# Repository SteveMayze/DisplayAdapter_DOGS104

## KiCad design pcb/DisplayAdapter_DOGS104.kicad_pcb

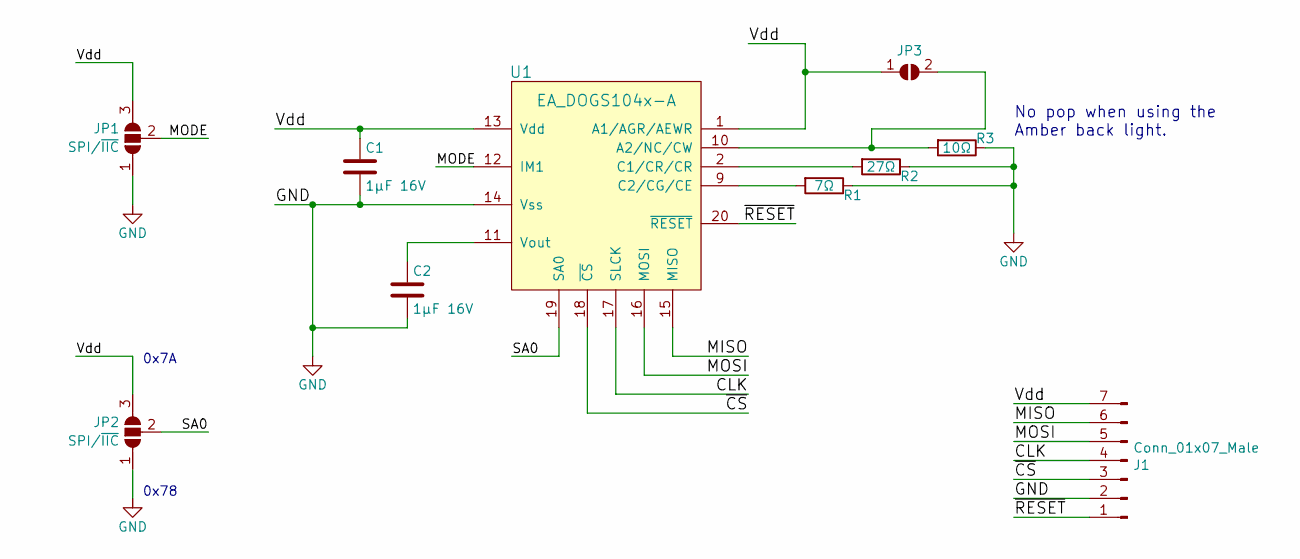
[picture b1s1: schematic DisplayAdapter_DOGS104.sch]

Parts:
C1, C2: 1μF 16V; C_0805_2012Metric_Pad1.15x1.40mm_HandSolder
J1: Conn_01x07_Male; PinHeader_1x07_P2.54mm_Horizontal
JP1, JP2: SPI/~IIC; SolderJumper-3_P1.3mm_Open_RoundedPad1.0x1.5mm_NumberLabels
JP3: SolderJumper_2_Open; SolderJumper-2_P1.3mm_Open_RoundedPad1.0x1.5mm
R1: 7Ω; R_0805_2012Metric_Pad1.15x1.40mm_HandSolder
R2: 27Ω; R_0805_2012Metric_Pad1.15x1.40mm_HandSolder
R3: 10Ω; R_0805_2012Metric_Pad1.15x1.40mm_HandSolder
U1: EA_DOGS104x-A

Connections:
/CLK: J1.4, U1.17 (SLCK~)
/MISO: J1.6, U1.15 (MISO)
/MODE: JP1.2 (C), U1.12 (IM1)
/MOSI: J1.5, U1.16 (MOSI)
/SA0: JP2.2 (C), U1.19 (SA0~)
/Vdd: C1.1, J1.7, JP1.3 (B), JP2.3 (B), JP3.1 (A), U1.1 (A1/AGR/AEWR), U1.13 (Vdd)
/~CS: J1.3, U1.18 (~CS)
/~RESET: J1.1, U1.20 (~RESET)
GND: C1.2, C2.2, J1.2, JP1.1 (A), JP2.1 (A), R1.1, R2.1, R3.1, U1.14 (Vss)
unnamed: C2.1, U1.11 (Vout)
unnamed: JP3.2 (B), R3.2, U1.10 (A2/NC/CW)
unnamed: R1.2, U1.9 (C2/CG/CE)
unnamed: R2.2, U1.2 (C1/CR/CR)

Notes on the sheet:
No pop when using the Amber back light.
0x7A
0x78

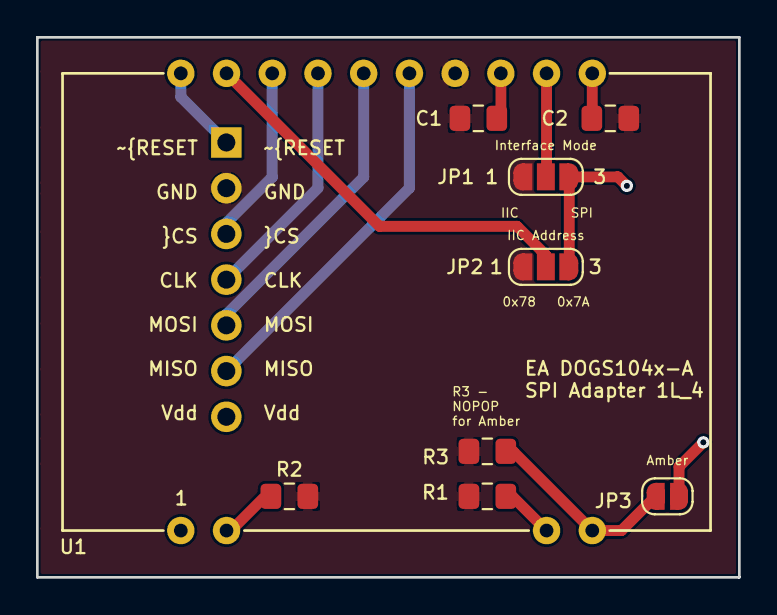
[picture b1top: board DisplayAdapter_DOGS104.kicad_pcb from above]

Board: 2 copper layers, 39.0 x 30.0 mm, 10 parts (1 on the bottom side), 13 nets.

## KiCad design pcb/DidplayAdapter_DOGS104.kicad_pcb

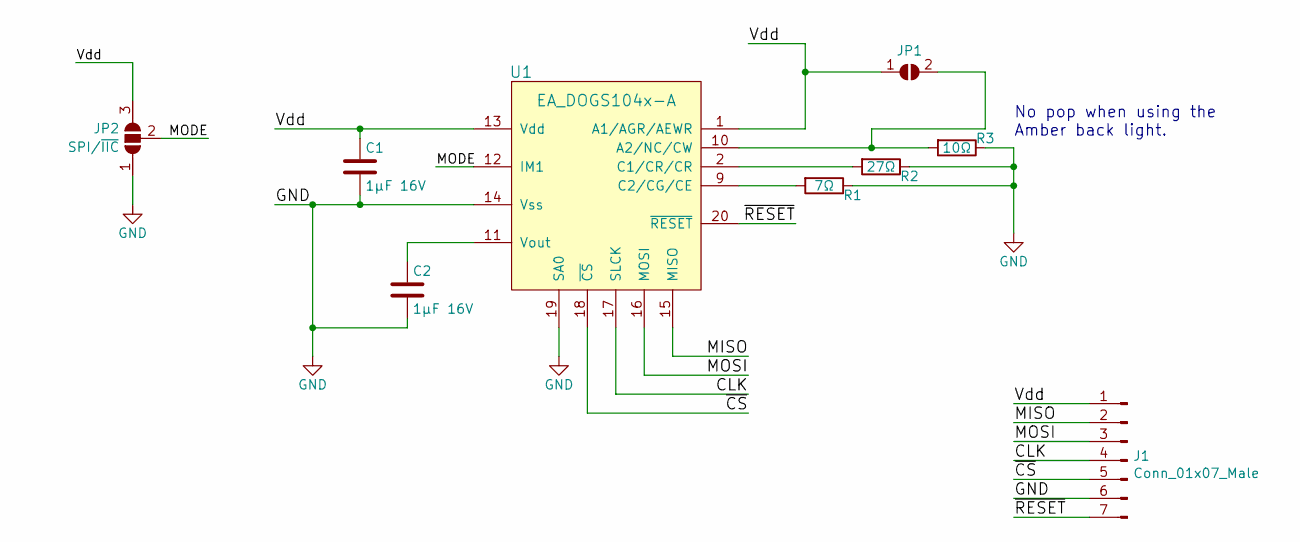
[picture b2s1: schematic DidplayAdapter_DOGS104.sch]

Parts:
C1, C2: 1μF 16V; C_0805
J1: Conn_01x07_Male; PinHeader_1x07_P2.54mm_Horizontal
JP1: SolderJumper_2_Open; SolderJumper-2_P1.3mm_Open_RoundedPad1.0x1.5mm
JP2: SPI/~IIC; SolderJumper-3_P1.3mm_Open_RoundedPad1.0x1.5mm_NumberLabels
R1: 7Ω; R_0805_HandSoldering
R2: 27Ω; R_0805_HandSoldering
R3: 10Ω; R_0805_HandSoldering
U1: EA_DOGS104x-A

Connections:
/CLK: J1.4, U1.17 (SLCK~)
/MISO: J1.2, U1.15 (MISO)
/MODE: JP2.2 (C), U1.12 (IM1)
/MOSI: J1.3, U1.16 (MOSI)
/Vdd: C1.1, J1.1, JP1.1 (A), JP2.3 (B), U1.1 (A1/AGR/AEWR), U1.13 (Vdd)
/~CS: J1.5, U1.18 (~CS)
/~RESET: J1.7, U1.20 (~RESET)
GND: C1.2, C2.2, J1.6, JP2.1 (A), R1.1, R2.1, R3.1, U1.14 (Vss), U1.19 (SA0~)
unnamed: C2.1, U1.11 (Vout)
unnamed: JP1.2 (B), R3.2, U1.10 (A2/NC/CW)
unnamed: R1.2, U1.9 (C2/CG/CE)
unnamed: R2.2, U1.2 (C1/CR/CR)

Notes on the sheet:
No pop when using the Amber back light.

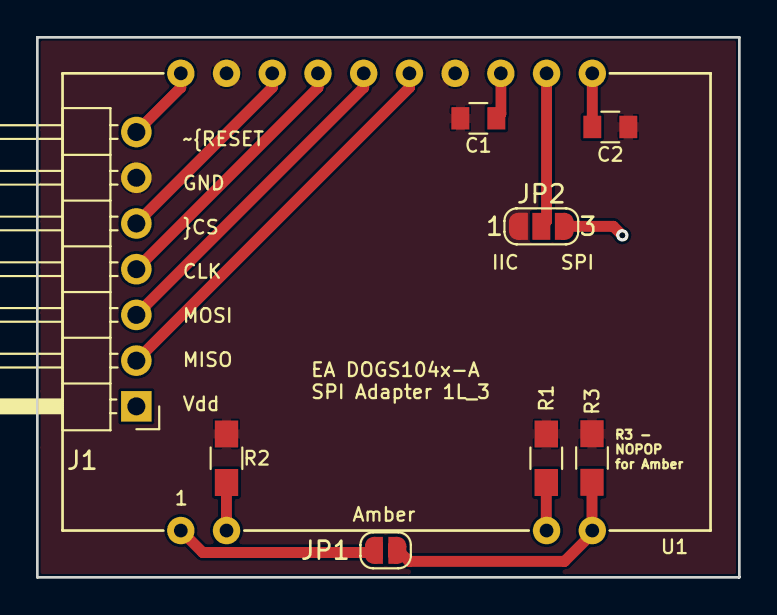
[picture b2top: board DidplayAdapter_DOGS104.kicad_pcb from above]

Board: 2 copper layers, 39.0 x 30.0 mm, 9 parts (0 on the bottom side), 12 nets.

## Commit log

2017-10-30 Initial commit - already sent to OSH Park
2017-10-31 Added a backlight resistor calculator
2018-01-08 Adding display documentation
2018-01-10 Migrated the arduino example from the field device
2018-01-11 Created a display test for the driver
2018-01-11 Removed the original experimental driver
2018-01-27 Complted the Rev2 layout and sent to OSHPark. Feature for back-light
2020-10-19 Uknown changes to merge with master
2020-10-21 Adds IIC address capability Rev 4
2020-10-21 Correction to the IIC address
